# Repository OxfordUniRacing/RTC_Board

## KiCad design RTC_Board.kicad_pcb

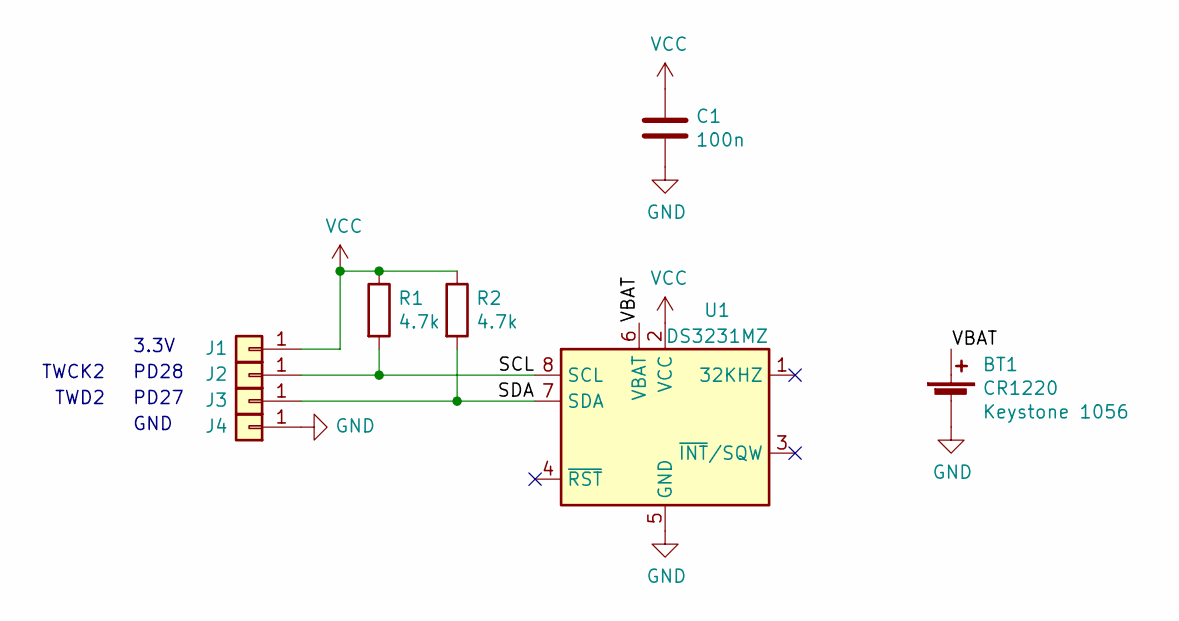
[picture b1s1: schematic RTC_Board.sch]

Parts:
BT1: CR1220; BatteryHolder_Keystone_1056_1x1220; Part Keystone 1056
C1: 100n; C_0805_2012Metric_Pad1.15x1.40mm_HandSolder
J1, J2, J3, J4: Conn_01x01; TestPoint_Pad_3.0x3.0mm
R1, R2: 4.7k; R_0805_2012Metric_Pad1.15x1.40mm_HandSolder
U1: DS3231MZ; SOIC-8_3.9x4.9mm_P1.27mm

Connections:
/SCL: J2.1, R1.2, U1.8 (SCL)
/SDA: J3.1, R2.2, U1.7 (SDA)
/VBAT: BT1.1 (+), U1.6 (VBAT)
GND: BT1.2 (-), C1.2, J4.1, U1.5 (GND)
VCC: C1.1, J1.1, R1.1, R2.1, U1.2 (VCC)

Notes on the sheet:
PD28
PD27
3.3V
GND
TWD2
TWCK2

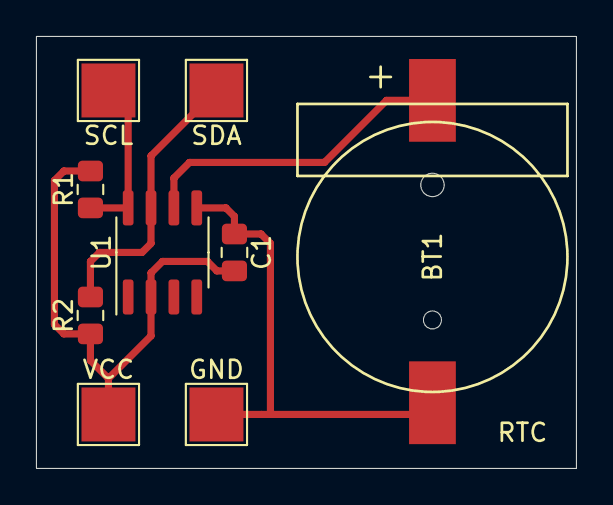
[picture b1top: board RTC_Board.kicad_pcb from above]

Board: 2 copper layers, 30.0 x 24.0 mm, 9 parts (0 on the bottom side), 5 nets.

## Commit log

2020-02-16 initial import
2020-02-19 decoupling cap
